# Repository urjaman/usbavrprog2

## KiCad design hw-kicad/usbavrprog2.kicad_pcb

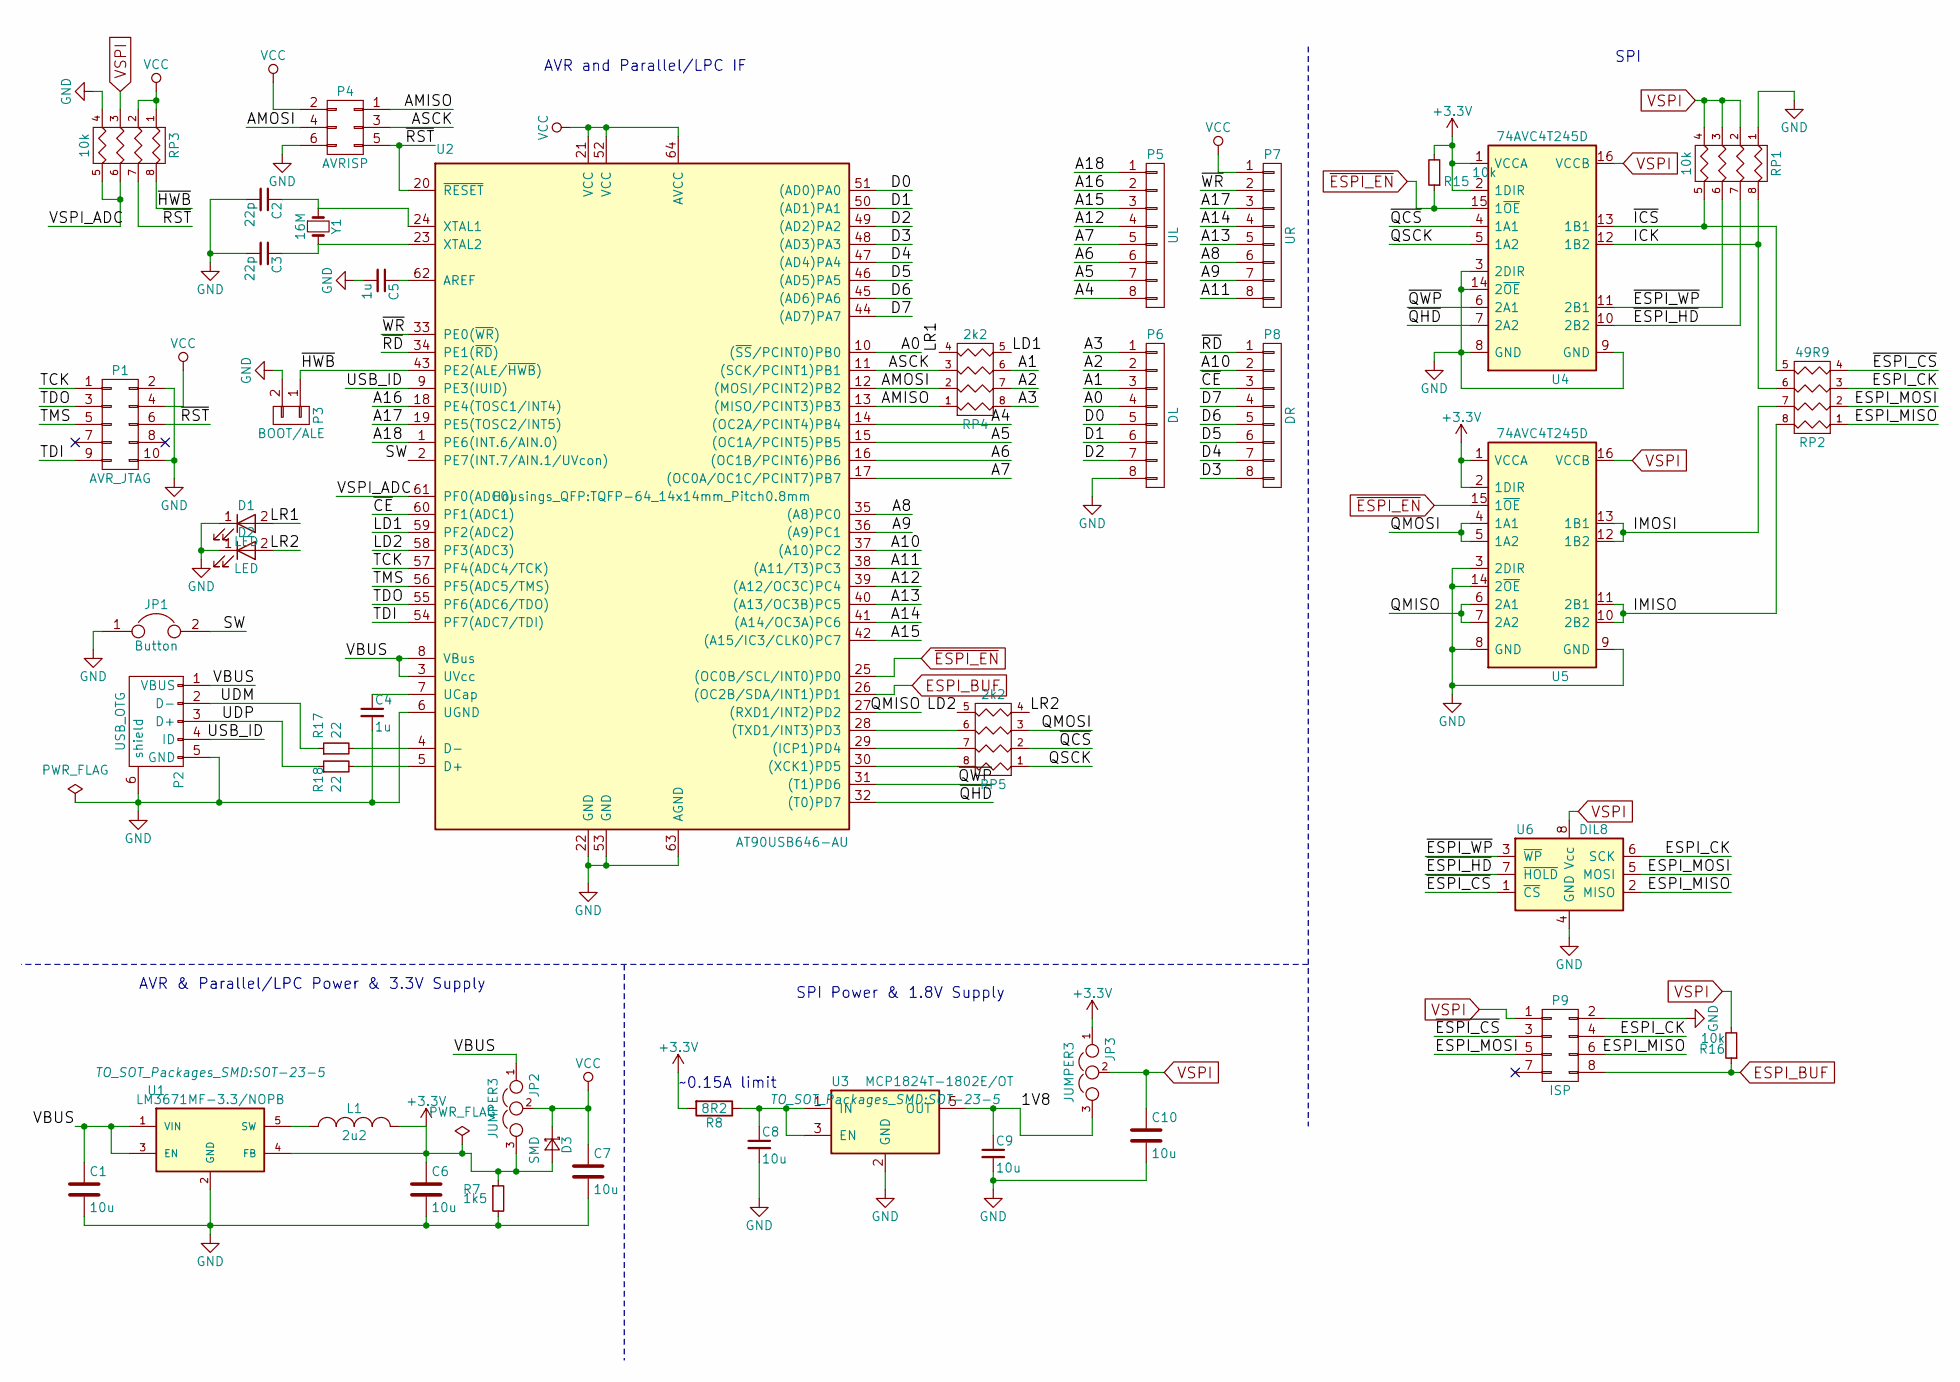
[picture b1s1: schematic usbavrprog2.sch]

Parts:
C1, C6, C7, C8, C9, C10: 10u; C_0805_HandSoldering
C2, C3: 22p; C_0603_HandSoldering
C4, C5: 1u; C_0603_HandSoldering
D1, D2: LED; LED_0603
D3: SMD; D_SOD-323_HandSoldering
JP1: Button; SW_PUSH_SMALL
JP2, JP3: JUMPER3; Pin_Header_Straight_1x03_Pitch2.54mm
L1: 2u2; R_0805_HandSoldering
P1: AVR_JTAG; Pin_Header_Straight_2x05_Pitch1.27mm
P2: USB_OTG; USB_Micro-B
P3: BOOT/ALE; Pin_Header_Straight_1x02_Pitch2.54mm
P4: AVRISP; Pin_Header_Straight_2x03_Pitch2.54mm
P5: UL; Pin_Header_Straight_1x08_Pitch2.54mm
P6: DL; Pin_Header_Straight_1x08_Pitch2.54mm
P7: UR; Pin_Header_Straight_1x08_Pitch2.54mm
P8: DR; Pin_Header_Straight_1x08_Pitch2.54mm
P9: ISP; Pin_Header_Straight_2x04_Pitch2.54mm
R7: 1k5; R_0603_HandSoldering
R8: 8R2; R_2512_HandSoldering
R15, R16: 10k; R_0603_HandSoldering
R17, R18: 22; R_0603_HandSoldering
RP1, RP3: 10k; R_Array_Concave_4x0603
RP2: 49R9; R_Array_Concave_4x0603
RP4, RP5: 2k2; R_Array_Concave_4x0603
U1: LM3671MF-3.3/NOPB; SOT-23-5
U2: AT90USB646-AU; TQFP-64_14x14mm_Pitch0.8mm
U3: MCP1824T-1802E/OT; SOT-23-5
U4, U5: 74AVC4T245D; SO-16-N
U6: DIL8; PDIP-8
Y1: 16M; Crystal_HC49-U_Vertical

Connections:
+3V3: C6.1, D3.2 (A), JP2.3, JP3.1, L1.2, R7.1, R8.2, R15.2, U1.4 (FB), U4.1 (VCCA), U4.2 (1DIR), U5.1 (VCCA), U5.2 (1DIR)
/1V8: C9.1, JP3.3, U3.5 (OUT)
/A0: P6.4, U2.10 ((~SS~/PCINT0)PB0)
/A1: P6.3, RP4.6 (R3)
/A2: P6.2, RP4.7 (R2)
/A3: P6.1, RP4.8 (R1)
/A4: P5.8, U2.14 ((OC2A/PCINT4)PB4)
/A5: P5.7, U2.15 ((OC1A/PCINT5)PB5)
/A6: P5.6, U2.16 ((OC1B/PCINT6)PB6)
/A7: P5.5, U2.17 ((OC0A/OC1C/PCINT7)PB7)
/A8: P7.6, U2.35 ((A8)PC0)
/A9: P7.7, U2.36 ((A9)PC1)
/A10: P8.2, U2.37 ((A10)PC2)
/A11: P7.8, U2.38 ((A11/T3)PC3)
/A12: P5.4, U2.39 ((A12/OC3C)PC4)
/A13: P7.5, U2.40 ((A13/OC3B)PC5)
/A14: P7.4, U2.41 ((A14/OC3A)PC6)
/A15: P5.3, U2.42 ((A15/IC3/CLK0)PC7)
/A16: P5.2, U2.18 (PE4(TOSC1/INT4))
/A17: P7.3, U2.19 (PE5(TOSC2/INT5))
/A18: P5.1, U2.1 (PE6(INT.6/AIN.0))
/AMISO: P4.1, RP4.1, U2.13 ((MISO/PCINT3)PB3)
/AMOSI: P4.4, RP4.2, U2.12 ((MOSI/PCINT2)PB2)
/ASCK: P4.3, RP4.3, U2.11 ((SCK/PCINT1)PB1)
/D0: P6.5, U2.51 ((AD0)PA0)
/D1: P6.6, U2.50 ((AD1)PA1)
/D2: P6.7, U2.49 ((AD2)PA2)
/D3: P8.8, U2.48 ((AD3)PA3)
/D4: P8.7, U2.47 ((AD4)PA4)
/D5: P8.6, U2.46 ((AD5)PA5)
/D6: P8.5, U2.45 ((AD6)PA6)
/D7: P8.4, U2.44 ((AD7)PA7)
/ESPI_CK: P9.4, RP2.3, U6.6 (SCK)
/ESPI_MISO: P9.6, RP2.1, U6.2 (MISO)
/ESPI_MOSI: P9.5, RP2.2, U6.5 (MOSI)
/ICK: RP1.8 (R1), RP2.6 (R3), U4.12 (1B2)
/IMISO: RP2.8 (R1), U5.10 (2B2), U5.11 (2B1)
/IMOSI: RP2.7 (R2), U5.12 (1B2), U5.13 (1B1)
/LD1: RP4.5 (R4), U2.59 (PF2(ADC2))
/LD2: RP5.5 (R4), U2.58 (PF3(ADC3))
/LR1: D1.2 (A), RP4.4
/LR2: D2.2 (A), RP5.4
/QMISO: U2.27 ((RXD1/INT2)PD2), U5.6 (2A1), U5.7 (2A2)
/QMOSI: RP5.3, U5.4 (1A1), U5.5 (1A2)
/QSCK: RP5.1, U4.5 (1A2)
/SW: JP1.2, U2.2 (PE7(INT.7/AIN.1/UVcon))
/TCK: P1.1, U2.57 (PF4(ADC4/TCK))
/TDI: P1.9, U2.54 (PF7(ADC7/TDI))
/TDO: P1.3, U2.55 (PF6(ADC6/TDO))
/TMS: P1.5, U2.56 (PF5(ADC5/TMS))
/UDM: P2.2 (D-), R17.1
/UDP: P2.3 (D+), R18.1
/USB_ID: P2.4 (ID), U2.9 (PE3(IUID))
/VBUS: C1.1, JP2.1, P2.1 (VBUS), U1.1 (VIN), U1.3 (EN), U2.3 (UVcc), U2.8 (VBus)
/VSPI_ADC: RP3.5 (R4), RP3.6 (R3), U2.61 (PF0(ADC0))
/~CE: P8.3, U2.60 (PF1(ADC1))
/~ESPI_CS: P9.3, RP2.4, U6.1 (~CS)
/~ESPI_HD: RP1.7 (R2), U4.10 (2B2), U6.7 (~HOLD)
/~ESPI_WP: RP1.6 (R3), U4.11 (2B1), U6.3 (~WP)
/~HWB: P3.1, RP3.8 (R1), U2.43 (PE2(ALE/~HWB~))
/~ICS: RP1.5 (R4), RP2.5 (R4), U4.13 (1B1)
/~QCS: RP5.2, U4.4 (1A1)
/~QHD: U2.32 ((T0)PD7), U4.7 (2A2)
/~QWP: U2.31 ((T1)PD6), U4.6 (2A1)
/~RD: P8.1, U2.34 (PE1(~RD~))
/~RST: P1.6, P4.5, RP3.7 (R2), U2.20 (~RESET)
/~WR: P7.2, U2.33 (PE0(~WR~))
ESPI_BUF: P9.8, R16.1, U2.26 ((OC2B/SDA/INT1)PD1)
GND: C1.2, C2.2, C3.2, C4.2, C5.2, C6.2, C7.2, C8.2, C9.2, C10.2, D1.1 (K), D2.1 (K), JP1.1, P1.2, P1.10, P2.5 (GND), P2.6 (shield), P3.2, P4.6, P6.8, P9.2, R7.2, RP1.1, RP3.4, U1.2 (GND), U2.6 (UGND), U2.22 (GND), U2.53 (GND), U2.63 (AGND), U3.2 (GND), U4.3 (2DIR), U4.8 (GND), U4.9 (GND), U4.14 (2~OE), U5.3 (2DIR), U5.8 (GND), U5.9 (GND), U5.14 (2~OE), U6.4 (GND)
unnamed: C2.1, U2.24 (XTAL1), Y1.1
unnamed: C3.1, U2.23 (XTAL2), Y1.2
unnamed: C4.1, U2.7 (UCap)
unnamed: C5.1, U2.62 (AREF)
unnamed: C8.1, R8.1, U3.1 (IN), U3.3 (EN)
unnamed: L1.1, U1.5 (SW)
unnamed: R17.2, U2.4 (D-)
unnamed: R18.2, U2.5 (D+)
unnamed: RP5.6 (R3), U2.28 ((TXD1/INT3)PD3)
unnamed: RP5.7 (R2), U2.29 ((ICP1)PD4)
unnamed: RP5.8 (R1), U2.30 ((XCK1)PD5)
VCC: C7.1, D3.1 (K), JP2.2, P1.4, P4.2, P7.1, RP3.1, RP3.2, U2.21 (VCC), U2.52 (VCC), U2.64 (AVCC)
VSPI: C10.1, JP3.2, P9.1, R16.2, RP1.2, RP1.3, RP1.4, RP3.3, U4.16 (VCCB), U5.16 (VCCB), U6.8 (Vcc)
~ESPI_EN: R15.1, U2.25 ((OC0B/SCL/INT0)PD0), U4.15 (1~OE), U5.15 (1~OE)

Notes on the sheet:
~~0.15A limit
AVR & Parallel/LPC Power & 3.3V Supply
SPI Power & 1.8V Supply
SPI
AVR and Parallel/LPC IF

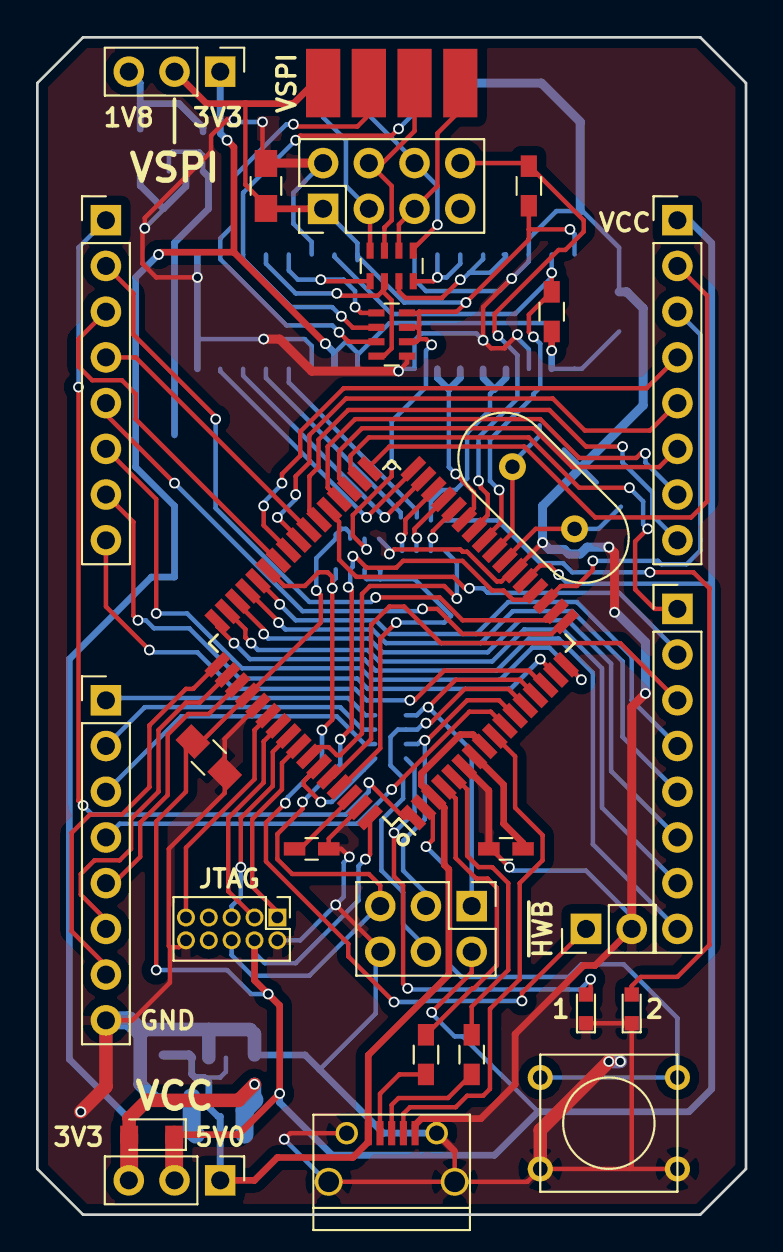
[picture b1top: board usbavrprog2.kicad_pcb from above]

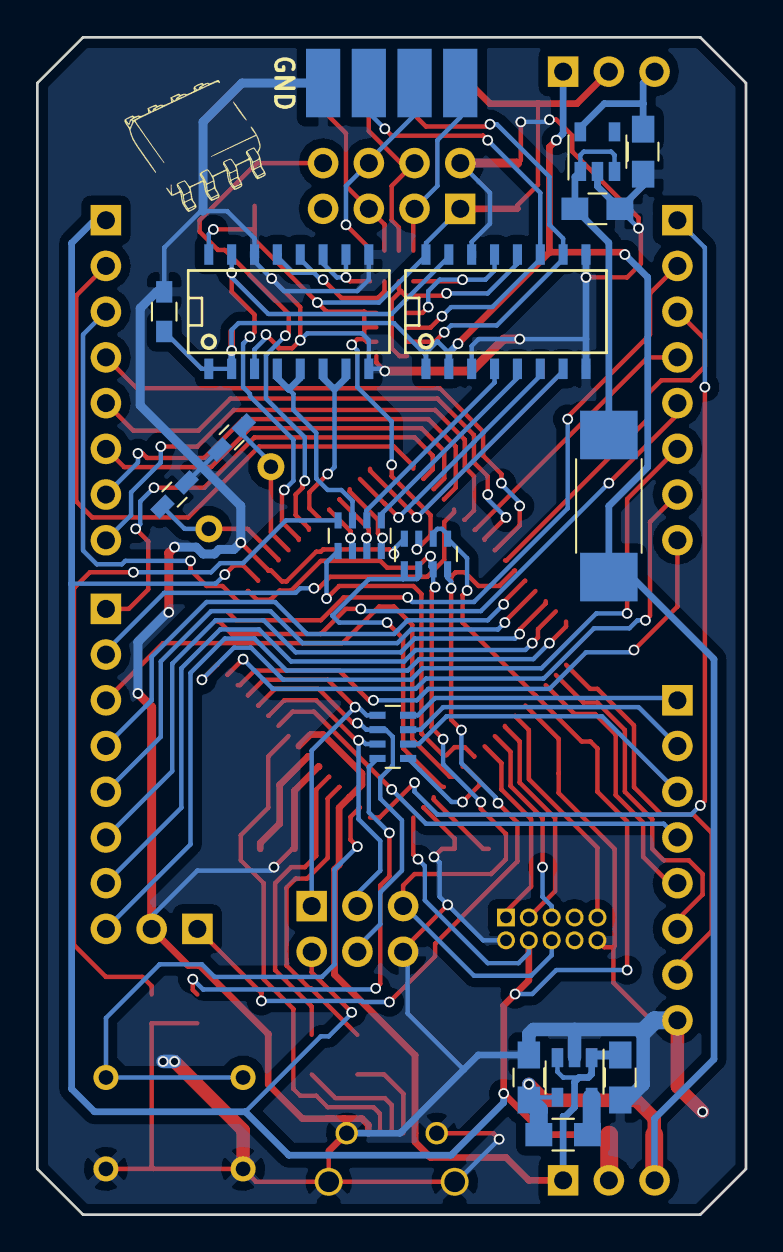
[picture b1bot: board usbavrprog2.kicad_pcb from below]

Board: 2 copper layers, 39.4 x 65.4 mm, 44 parts (16 on the bottom side), 83 nets.

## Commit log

2015-10-02 Give git libfrser info ...
2015-10-02 This is what happens when you take frser-duino and fast-usbserial and splash them together
2015-10-02 Now it works, has about 4MBaud uart equivalent read speed...
2015-10-02 Remove old readme data
2015-10-02 Change the name to better suit the genericity of what we have ...
2017-08-12 pre-test-work on usbavrprog2
2017-08-14 oh, it runs...
    sadly to use the isp way (and set the fuses right) i had
    to wipe the dfu... wonder if thats available anywhere...
    OTOH i guess i could get a more FOSS bootloader for it
2017-08-15 switch to jtag w/ the atmelice, cleanup of descriptors
2017-08-15 rework the accelerated usb uart "API" a little saner
2017-08-20 cant make gcc do what i want, but i guess it"s close enough
2017-08-20 Add the console interface so we can debug better
2017-08-21 pretty code over pretty asm, and well the asm isnt thaat bad
2017-08-21 add local commands file and first command (VSPI)
2017-08-21 add vcc measurement command while at it
2017-08-24 add an override command interface for the spi signals
    this is for hardware debugging, if you use this for
    anything else i will apply a big trout on you
2017-08-24 something something reference changes...
2017-08-24 Add kicad hardware design files
    the files for the daughter boards arent here yet since they're
    recycled from usbavrprog1 (which is from my EAGLE era...)
2017-08-24 move the ADC code into its own module
    It implements a very simplistic yet high level interface
2017-08-24 implement LEDs while converting some files out of dos format
2017-08-24 pass the thing through astyle
    dear lord the LUFA stuff still needs work to be sane...
2017-08-24 apparently this WIP stuff improved perf, so lets put it in
2017-08-24 Faster!
    Tbh, 2seconds faster for a 16M chip (27s -> 25s), so now
    at 5.242M / 8M (up from 4.74M). Which is still just 65%
    of what we should be capable of....
2017-08-24 not expecting to use eeprom for usb things...
2019-03-20 Improve SPI debug abilities
    this debug command makes it pretty simple to test the drivers
    just with a 3-wire loopback on the SPI port
2019-03-26 fix SPI_EN pin handling
    that pin was not supposed to be driven high
2019-03-26 Add support for running the MCU at 3.3V (8 Mhz)
    This just detects the VCC voltage on boot and selects
    the appropriate mode. Future considerations include
    hooking up libfrser to ramp up/down based on usage
    (could just use the bus drivers enable/disable for that really.)
